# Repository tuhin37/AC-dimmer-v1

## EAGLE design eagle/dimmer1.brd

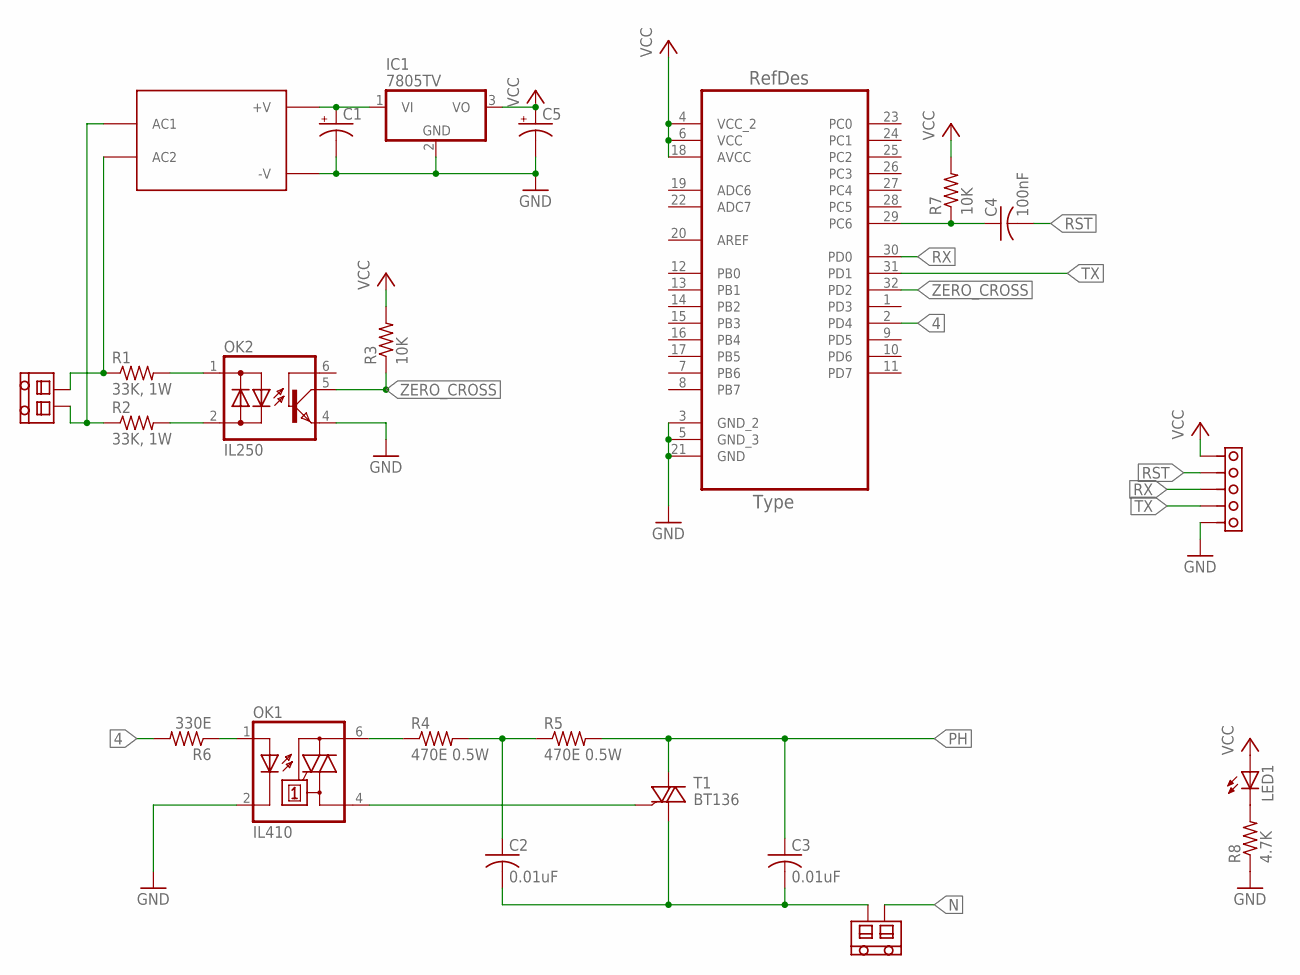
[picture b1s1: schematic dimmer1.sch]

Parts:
C1, C5: CPOL-US153CLV-0807; 153CLV-0807
C2, C3: 0.01uF; C075-032X103
C4: 100nF; C1206
IC1: 7805TV; TO220V
LED1: LEDCHIPLED_1206; CHIPLED_1206
OK1: IL410; DIL06
OK2: IL250; DIL06
R1, R2: 33K, 1W; 0207/10
R3, R7: 10K; M1206
R4, R5: 470E 0.5W; 0207/12
R6: 330E; M1206
R8: 4.7K; M1206
T1: BT136; TO220AB
U1: ATMEGA328P-AU; QFP80P900X900X120-32N
U$1: DC_ADAPTER
U$2, U$3: TERMINAL_BLOCK
U$4: BERG_5

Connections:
4: R6.2, U1.2 (PD4)
GND: C1.-, C5.-, IC1.2 (GND), OK1.2 (C), OK2.4 (E), R8.1, U1.3 (GND_2), U1.5 (GND_3), U1.21 (GND), U$1.V- (-V), U$4.E
N: R2.1, U$1.AC1, U$2.1, U$3.1
unnamed: OK2.1 (AC1), R1.2
unnamed: OK1.1 (A), R6.1
unnamed: LED1.C, R8.2
unnamed: OK2.2 (AC2), R2.2
unnamed: C1.+, IC1.1 (VI), U$1.V+ (+V)
unnamed: OK1.6 (A2), R4.1
unnamed: C2.1, R4.2, R5.1
unnamed: C2.2, C3.2, T1.1 (A1), U$3.2
unnamed: OK1.4 (A1), T1.3 (G)
PH: C3.1, R1.1, R5.2, T1.2 (A2), U$1.AC2, U$2.2
RS: C4.1, R7.1, U1.29 (PC6)
RST: C4.2, U$4.H
RX: U1.30 (PD0), U$4.G
TX: U1.31 (PD1), U$4.F
VCC: C5.+, IC1.3 (VO), LED1.A, R3.2, R7.2, U1.4 (VCC_2), U1.6 (VCC), U1.18 (AVCC), U$4.I
ZERO_CROSS: OK2.5 (C), R3.1, U1.32 (PD2)

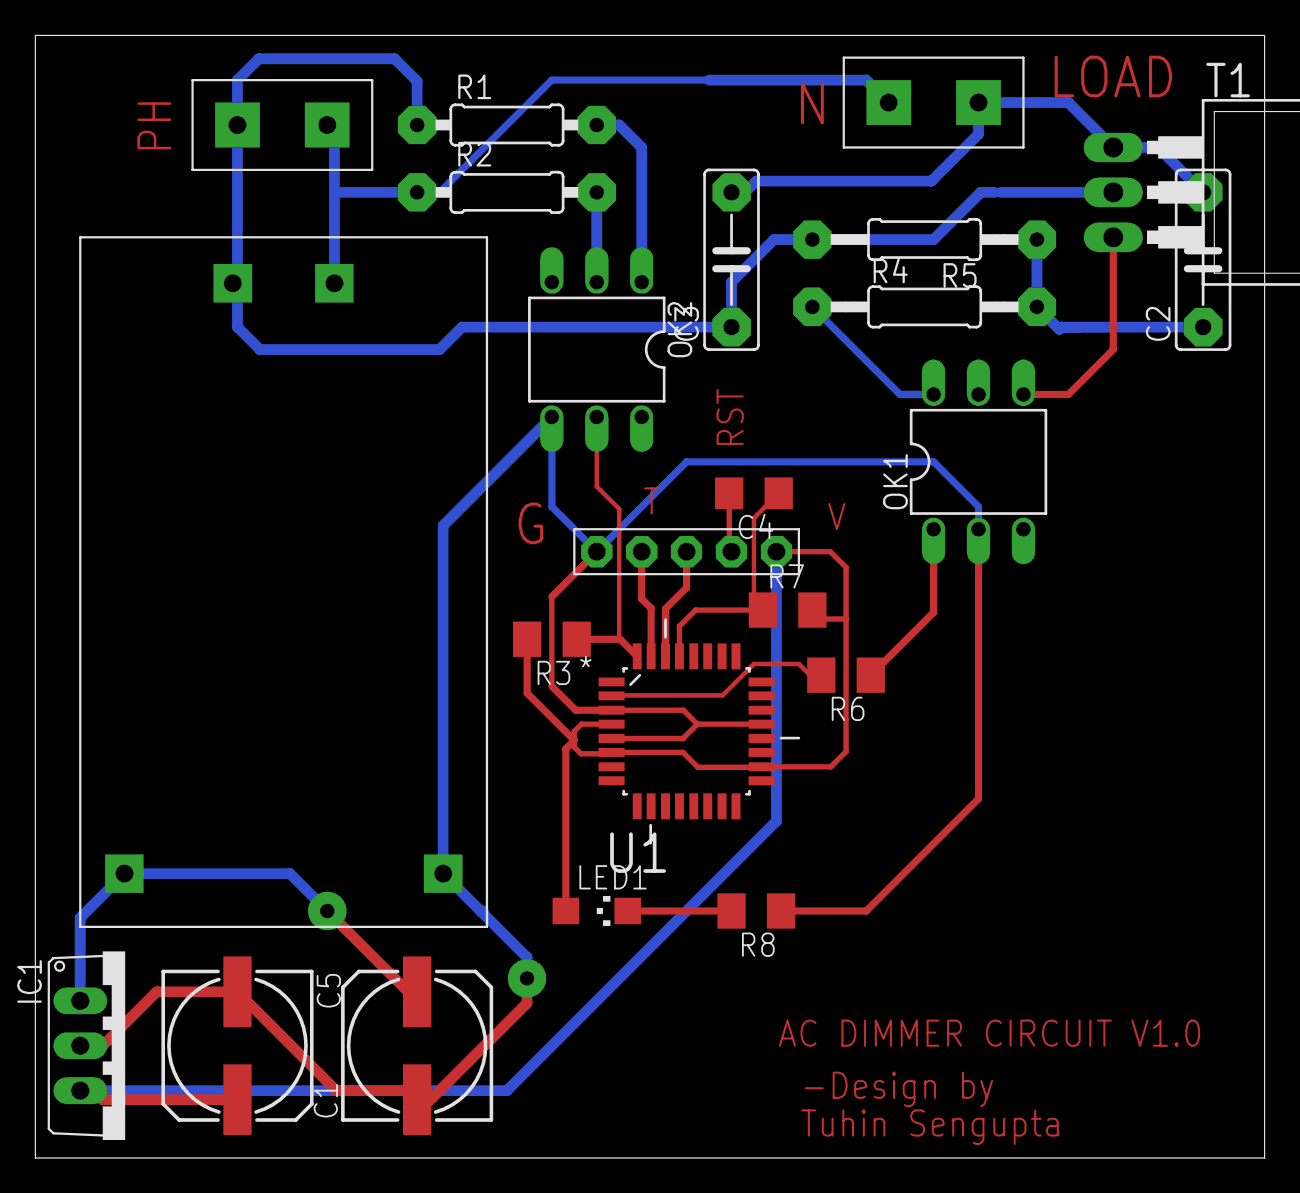
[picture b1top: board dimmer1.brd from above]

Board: 2 copper layers, 69.5 x 63.5 mm, 23 parts (0 on the bottom side), 19 nets.

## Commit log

2018-12-16 Add: Initial add
2018-12-16 Add: Arduino code
2018-12-17 Comment: results added in a note
